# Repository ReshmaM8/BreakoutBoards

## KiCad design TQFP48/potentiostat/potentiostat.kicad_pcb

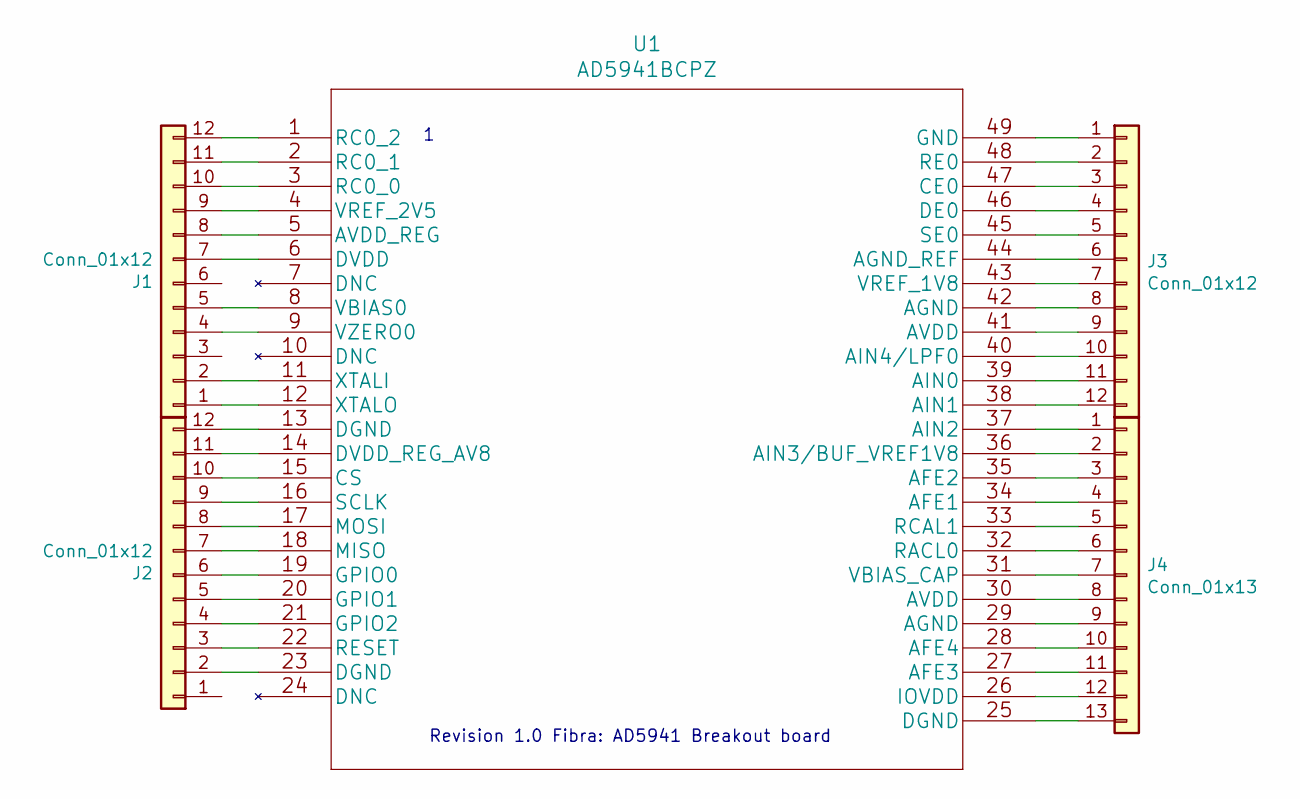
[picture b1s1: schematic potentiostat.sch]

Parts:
J1, J2, J3: Conn_01x12; PinHeader_1x12_P1.00mm_Vertical
J4: Conn_01x13; PinHeader_1x13_P1.00mm_Vertical
U1: AD5941BCPZ

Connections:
unnamed: J1.1, U1.12 (XTALO)
unnamed: J1.2, U1.11 (XTALI)
unnamed: J1.4, U1.9 (VZERO0)
unnamed: J1.5, U1.8 (VBIAS0)
unnamed: J1.7, U1.6 (DVDD)
unnamed: J1.8, U1.5 (AVDD_REG)
unnamed: J1.9, U1.4 (VREF_2V5)
unnamed: J1.10, U1.3 (RC0_0)
unnamed: J1.11, U1.2 (RC0_1)
unnamed: J1.12, U1.1 (RC0_2)
unnamed: J2.2, U1.23 (DGND)
unnamed: J2.3, U1.22 (RESET)
unnamed: J2.4, U1.21 (GPIO2)
unnamed: J2.5, U1.20 (GPIO1)
unnamed: J2.6, U1.19 (GPIO0)
unnamed: J2.7, U1.18 (MISO)
unnamed: J2.8, U1.17 (MOSI)
unnamed: J2.9, U1.16 (SCLK)
unnamed: J2.10, U1.15 (CS)
unnamed: J2.11, U1.14 (DVDD_REG_AV8)
unnamed: J2.12, U1.13 (DGND)
unnamed: J3.1, U1.49 (GND)
unnamed: J3.2, U1.48 (RE0)
unnamed: J3.3, U1.47 (CE0)
unnamed: J3.4, U1.46 (DE0)
unnamed: J3.5, U1.45 (SE0)
unnamed: J3.6, U1.44 (AGND_REF)
unnamed: J3.7, U1.43 (VREF_1V8)
unnamed: J3.8, U1.42 (AGND)
unnamed: J3.9, U1.41 (AVDD)
unnamed: J3.10, U1.40 (AIN4/LPF0)
unnamed: J3.11, U1.39 (AIN0)
unnamed: J3.12, U1.38 (AIN1)
unnamed: J4.1, U1.37 (AIN2)
unnamed: J4.2, U1.36 (AIN3/BUF_VREF1V8)
unnamed: J4.3, U1.35 (AFE2)
unnamed: J4.4, U1.34 (AFE1)
unnamed: J4.5, U1.33 (RCAL1)
unnamed: J4.6, U1.32 (RACL0)
unnamed: J4.7, U1.31 (VBIAS_CAP)
unnamed: J4.8, U1.30 (AVDD)
unnamed: J4.9, U1.29 (AGND)
unnamed: J4.10, U1.28 (AFE4)
unnamed: J4.11, U1.27 (AFE3)
unnamed: J4.12, U1.26 (IOVDD)
unnamed: J4.13, U1.25 (DGND)

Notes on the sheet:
Revision 1.0 Fibra: AD5941 Breakout board

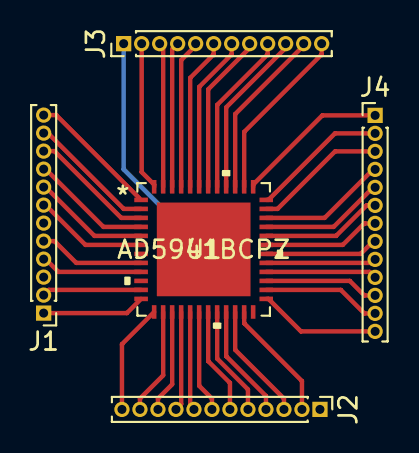
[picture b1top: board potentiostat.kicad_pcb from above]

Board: 2 copper layers, 5 parts (0 on the bottom side), 46 nets.

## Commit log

2022-12-02 potentiostat AD5941 added
2022-12-02 add better connections(3 12pin 1 13 pin generic pin headers)

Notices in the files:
parts and their libraries:
Copyright 2021 Accelerated Designs. All rights reserved.
